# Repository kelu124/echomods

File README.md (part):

# What is this project? 

This project has a specific target of providing a __low-cost, open source technological kit to allow scientists, academics, hackers, makers or OSHW fans to hack their way to ultrasound imaging__ - below 500$ - at home, with no specific equipment required. For complementary sources of information, you can visit:

* the [github repo](https://github.com/kelu124/echomods/), for the source files, raw data and raw experiment logs;
* the [online manual/book](https://www.gitbook.com/book/kelu124/echomods/details) for a easily readable and searchable archive of the whole work;
  * with [list of probes](/include/probes/)
  * and [list of experiments](/include/experiments/)
* the [hackaday page](https://hackaday.io/project/9281-murgen-open-source-ultrasound-imaging), where I tried to blog day-to-day experiments in a casual format;
* an [article summarizing the experiment on the Journal of Open Hardware](http://openhardware.metajnl.com/articles/10.5334/joh.2/) - [DOI:10.5334/joh.2]( http://doi.org/10.5334/joh.2);
* the [slack channel if you want to discuss](https://join.slack.com/t/usdevkit/shared_invite/zt-2g501obl-z53YHyGOOMZjeCXuXzjZow);
* the Tindie store for the [analog processing unit](https://www.tindie.com/products/kelu124/ultrasound-imaging-analog-processing-module/) and the [unipolar pulser](https://www.tindie.com/products/kelu124/ultrasound-unipolar-high-voltage-pulser/) or [the motherboard](https://www.tindie.com/products/kelu124/ultrasound-modules-motherboard/).
* And of course, the [ice40 research board](https://www.tindie.com/products/kelu124/un0rick-open-ice40-ultrasound-imaging-dev-board/), on [un0rick.cc](http://un0rick.cc) and its [doc](http://doc.un0rick.cc) or even [its github](https://github.com/kelu124/un0rick). _It's a bit cheaper, and has better specs_. 

* __Disclaimer #0__: __This is not a medical ultrasound scanner__! It's a development kit that can be used for pedagogical and academic purposes - possible immediate use as a non-destructive testing (NDT) tool, for example in metallurgical crack analysis. As in all electronics, be [careful](/WordOfCaution.md).
* __Disclaimer #1__: though an engineer, this project is the first of its sort, I never did something related. It's all but a finalized product.
* __Disclaimer #2__: Ultrasound raises questions. In case you build a scanner, use caution and good sense!
* __Disclaimer #3__: This project is not part of echopen.

# Principles of ultrasound imaging

## General principles of ultrasound imaging

### Using echoes to map interfaces

Medical ultrasound is based on the use of high frequency sound to aid in the diagnosis and treatment of patients. Ultrasound frequencies range from 2 MHz to approximately 15 MHz, although even higher frequencies may be used in some situations.

The ultrasound beam originates from mechanical oscillations of numerous crystals in a transducer, which are excited by electrical pulses (piezoelectric effect). The transducer converts one type of energy into another (electrical <--> mechanical/sound). 

The ultrasound waves (pulses of sound) are sent from the transducer, propagate through different tissues, and then return to the transducer as reflected echoes when crossing an interface. The returned echoes are converted back into electrical impulses by the transducer crystals and are further processed - _mostly to extract the enveloppe of the signal, a process that transforms the electrical signal in an image_ -  in order to form the ultrasound image presented on the screen.

Ultrasound waves are reflected at the surfaces between the tissues of different density, the reflection being proportional to the difference in impedance. If the difference in density is increased, the proportion of reflected sound is increased and the proportion of transmitted sound is proportionately decreased.

If the difference in tissue density is very different, then sound is completely reflected, resulting in total acoustic shadowing. Acoustic shadowing is present behind bones, calculi (stones in kidneys, gallbladder, etc.) and air (intestinal gas). Echoes are not produced on the other hand if there is no difference in a tissue or between tissues. Homogenous fluids like blood, bile, urine, contents of simple cysts, ascites and pleural effusion are seen as echo-free structures.

### Creating a 2D image

If the process is repeated with the probe sweeping the area to image, one can build a 2D image. In practice, in the setups we'll be discussing, this sweep is done with a transducer coupled to a servo, or using a probe that has an built-in motor to create the sweep.

# Necessary architecture

### Transducer

A critical component of this system is the ultrasound transducer. A typical ultrasound imaging system uses a wide variety of transducers optimized for specific diagnostic applications, but in our case, we'll limit the costs.
 
### High-Voltage Transmitters ([see the module](/retired/tobo/))

A digital transmit beamformer typically generates the necessary digital transmit signals with the proper timing and phase to produce a focused transmit signal. High-voltage pulsers quickly switch the transducer element to the appropriate programmable high-voltage supplies to generate the transmit waveform. To generate a simple bipolar transmit waveform, a transmit pulser alternately connects the element to a positive and negative transmit supply voltage controlled by the digital beamformer. More complex realizations allow connections to multiple supplies and ground in order to generate more complex multilevel waveforms with better characteristics.

### TGC + LNA = Variable-Gain Amplifier (VGA) ([see the module](/goblin/))

The LNA in the receiver must have excellent noise performance and sufficient gain. In a properly designed receiver the LNA will generally determine the noise performance of the full receiver. 

The VGA, sometimes called a time gain control (TGC) amplifier, provides the receiver with sufficient dynamic range over the full receive cycle. Ultrasound signals propagate in the body at approximately 1540 meters per second and attenuate at a rate of about 1.4dB/cm-MHz roundtrip. Immediately after an acoustic transmit pulse, the received "echo" signal at the LNA's input can be as large as 0.5VP-P. This signal quickly decays to the thermal noise floor of the transducer element. The dynamic range required to receive this signal is approximately 100dB to 110dB, and is well beyond the range of a realistic ADC. As a result, a VGA is used to map this signal into the ADC. A VGA with approximately 30dB to 40dB of gain is necessary to map the received signal into a typical 12-bit ADC used in this application. The gain is ramped as a function of time (i.e., "time gain control") to accomplish this dynamic range mapping.

### Anti-Alias Filter (AAF) and ADC ([see the module](/retired/toadkiller/))

The AAF in the receive chain keeps high-frequency noise and extraneous signals that are beyond the normal maximum imaging frequencies from being aliased back to baseband by the ADC. Many times an adjustable AAF is provided in the design. To avoid aliasing and to preserve the time-domain response of the signal, the filter itself needs to attenuate signals beyond the first Nyquist zone. For this reason Butterworth or higher-order Bessel filters are used.

The ADC used in this application is typically a 12-bit device running from 40Msps to 60Msps. This converter provides the necessary instantaneous dynamic range at acceptable cost and power levels. In a properly designed receiver, this ADC should limit the instantaneous SNR of the receiver. As previously mentioned, however, limitations in the poor-performing VGAs many times limit receiver SNR performance

## Ultrasound hardware structure

To produce an image, the modules have to create a [high voltage pulse](/retired/tobo/), which excites a [transducer](/retroATL3/). Echoes coming from the body are amplified using a [TGC + LNA](/goblin/), which cleans the analog signal, which itself [gets digitalized](/retired/toadkiller/). 

The diagram is represented below:

# Un0rick, the ice40 board

## Why a FPGA board ?

Non destructive testing and imaging ultrasound modalities have been around since the '50s in . More and more ultrasound-based initiative are emerging, mostly focusing on image processing - while hardware has been left behind. Several teams have produced succesful designs for the different possible uses, mostly efforts from research laboratories. Most have been used on commercial US scanners, traditionaly used as experiment platforms, but they are not cheap, and yield very little in terms of data access and control. Others have been developped in labs, but, sadly, very few have been open-sourced. Let's tackle this!

It has also been shown that simple (be it low-power, low-cost and small) can be achieved - and this, even for relatively complex systems, based on 16 to 64  parallel   channels   front-end  processing and software back-end processing (embedded PC or DSP). This makes it a bit more complex for the layman, hobbyist, or non-specialist researcher to use, not to mention the very little information that is accessible.

## Hardware specifications and features

1. __FPGA__: Lattice iCE40HX4K - TQFP 144 Package
2. __Memory__:
  * 8 Mbit SRAM, 10ns, 512 k x 16, equivalent:
      * 65 full lines of 120us at 64Msps
      * 840 lines of 120us at 10Msps, 8 bits
  * 8 Mb SPI Flash for FPGA configuration 
3. __Ultrasound processing__:
  * __VGA__: AD8331 controled by DAC
  * __Pulser__: MD1210 + TC6320
  * __ADC__: 65Msps ADC10065
    * 10 bits of data / sample
    * 2 bits of line counters
    * 4 bits of IOs (counters, ...) 
4. __Parameters__: Settings programable via USB or Raspberry Pi 
  * Type of acquisition (one line / set of lines)
  * Number of lines
  * Length of lines acquisitions
  * Delay between acquisitions
  * Pulse width 
  * Delay between pulse and beginning of acquisitions
  * 200us time-gain-compensation programmable (8 bits, from 0 to Max), every 5us
5. __Extensibility__:
  * 2 x Pmod connectors
  * SMA plug for transducers
  * RPi GPIO
6. __User Interfaces__:
  * 2 x PMOD for IOs
  * 3 x push button (with software noise debouncing)
  * Jumpers for high voltage selection
7. __Input Voltage__: 
  * 5 V from RPi or USB
  * Uses 350mA-450mA at 5V
8. __Fully Open Source__:
  * Hardware: _github repository_
  * Software: _github repository_
  * Toolchain: _Project IceStorm_
  * Documentation: _gitbook_
9. __Operating Voltage__: 
  * FPGA and logics at at 3.3 V
  * High voltage at 25V, 50V, 75V
10. __Dimensions__: @todo!
11. __Weight__: @todo! 

## Comparative

| Tool           	| Murgen 	| echOmods        	| unoric               	|
|----------------	|--------	|-----------------	|----------------------	|
| Open Source    	| Yes    	| Yes             	| Yes                  	|
| ADC            	| 20Msps 	| 1Msps to 24Msps 	| 65Msps up to 100Msps 	|
| Onboard memory 	| 300 Mb 	| 10 Mb           	| 20Mb                 	|
| Price of a set	| 400$		| 450$			| 400$			|
| Modular		| Np		| Yes			| No			| 

# Modules

## What are the arduino-like ultrasound module ?

__Creating modules to facilitate ultrasound hacking__ : the principles of the echOmods is to enable a full chain of ultrasound image processing and hardware control.

We have chosen to use a module approach to make sure that each key component inside ultrasound image processing can easily be replaced and compared with another module, while providing logical _logic blocks_ and corresponding interfaces for these modules to communicate. There's a module for [high-voltage pulsing](/retired/tobo/), one for the [transducer](/retroATL3/), one for the [analog processing](/goblin/), one for [data acquisiton](/retired/toadkiller/), ... and many more!

## What images does it give ?

## What does it look like?

The modules sit on a breadboard, and communicate through the tracks laying below. The configuration represented below show the Basic dev kit.

and used in a wider context:

# A recap of the modules 

| ThumbnailImage | Name | In | Out |
|------|-------|----|------|
||**[retroATL3](/retroATL3/Readme.md)**: The aim of this echOmod is to get the mechanical movement of the piezos. Salvaged from a former ATL3.|<ul><li>ITF-A_gnd</li><li>ITF-F_12V</li><li>ITF-N_cc_motor_pwm</li><li>ITF-mET_Transducer</li><li>Motor</li><li>Tri-Piezo Head</li></ul>|<ul><li>Motor</li><li>ITF-mET_Transducer</li><li>Tri-Piezo Head</li></ul>|
||**[elmo](/elmo/Readme.md)**: The aim of this module is to achieve 20Msps, at 9bits or more. |<ul><li>ITF-1_GND</li><li>ITF-2_VDD_5V</li><li>ITF-19_3.3V</li><li>ITF-12_RPIn</li></ul>|<ul><li>Signal Digitalized</li></ul>|
||**[goblin](/goblin/Readme.md)**: The aim of this echOmod is to get the signal coming back from a transducer, and to deliver the signal, analogically processed, with all steps accessible to hackers. |<ul><li>ITF-1_GND</li><li>ITF-2_VDD_5V</li><li>ITF-7_GAIN</li><li>ITF-4_RawSig</li><li>ITF-3_ENV</li><li>ITF-18_Raw</li><li>ITF-mET_SMA</li></ul>|<ul><li>ITF-4_RawSig</li><li>ITF-3_ENV_signal_envelope</li><li>ITF-mEG_SPI</li></ul>|
||**[lite.tbo](/lite.tbo/Readme.md)**: The aim of this echOmod is to get the HV Pulse done.|<ul><li>ITF-1_GND</li><li>ITF-2_VDD_5V</li><li>ITF-9_Pon</li><li>ITF-10_Poff</li><li>ITF-19_3.3V</li><li>ITF-mET_Transducer</li></ul>|<ul><li>ITF-18_Raw</li><li>ITF-mET_SMA</li><li>ITF-mET_Transducer</li></ul>|
||**[lit3rick](/lit3rick/Readme.md)**: The aim is to summarize all modules in a all-inclusive board. Fast ADC, good load of memory, good SNR.. the not-so-DIY module, as it comes already assembled with nothing to do. Based on up5k.|||
||**[matty](/matty/Readme.md)**: The aim is to summarize all modules in a all-inclusive board. Fast ADC, good load of memory, good SNR.. the not-so-DIY module, as it comes already assembled with nothing to do =)|||
||**[doj](/doj/Readme.md)**: Getting a motherboard: that's fitting all the modules in an easy way, with an easy access to all tracks. See this for the Kicad files.|||
||**[wirephantom](/wirephantom/Readme.md)**: Just a phantom for calibrated signals|<ul><li>na</li></ul>|<ul><li>na</li></ul>|
||**[silent](/silent/Readme.md)**: The aim of this echOmod is to simulate a raw signal that would come from the piezo and analog chain.|<ul><li>ITF-1_GND</li><li>ITF-2_VDD_5V</li><li>ITF-17_POff3</li></ul>|<ul><li>ITF-18_Raw</li></ul>|

# List of experiments

# Experiments

 * 2021-04-25: [Annular MUXed](/include/experiments/auto/20210425a.md): testing an annular transducer on a pink phantom _(20210425a)_
 * 2021-04-24: [BiVi piezo on the MUX](/include/experiments/auto/20210424a.md): First tests of the MUX _(20210424a)_
 * 2021-01-29: [`Tri` two probes](/include/experiments/auto/20210129a.md): Tri's tests with two probes _(20210129a)_
 * 2020-12-23: [test probes](/include/experiments/auto/20201223a.md): testing probes with un0usb _(20201223a)_
 * 2020-12-19: [test piezos](/include/experiments/auto/20201219r.md): VNAs piezos (dismanted ones) _(20201219r)_
 * 2020-11-28: [hp2121 matching](/include/experiments/auto/20201128a.md): checking hp2121 probe impedance matching _(20201128a)_
 * 2020-11-08: [impedance matching](/include/experiments/auto/20201108a.md): testing two piezos with impedance matching network _(20201108a)_
 * 2020-11-07: [lib 025](/include/experiments/auto/20201107a.md): NDT presentation - un0rick & usb _(20201107a)_
 * 2020-11-04: [lib 024](/include/experiments/auto/20201104a.md): Basics on - un0rick & usb _(20201104a)_
 * 2020-11-03: [Impedance matching](/include/experiments/auto/20201103a.md): Interesting results for impedance matching. _(20201103a)_
 * 2020-10-31: [Pulse width calculation](/include/experiments/auto/20201031a.md): how to get the best echo as a function of pulser waveform _(20201031a)_
 * 2020-10-28: [strange issues pyUn0](/include/experiments/auto/20201028a.md): seems CS does not work _(20201028a)_
 * 2020-10-26: [usb firmware](/include/experiments/auto/20201026a.md): testing it works with un0rick _(20201026a)_
 * 2020-10-24: [i2s issue](/include/experiments/auto/20201024a.md): Exploring the i2s offsets _(20201024a)_
 * 2020-10-23: [Canada](/include/experiments/auto/20201023a.md): `Silvio` first lit3rick tests _(20201023a)_
 * 2020-10-22: [Spain](/include/experiments/auto/20201022a.md): `Jorge` tests on lit3rick _(20201022a)_
 * 2020-10-08: [benchmark lit3 and un0](/include/experiments/auto/20201008a.md): Running acquisitions on the same rig. _(20201008a)_
 * 2020-08-09: [bard vna](/include/experiments/auto/20200809r.md): bard vna tests _(20200809r)_
 * 2020-08-08: [all probes vna](/include/experiments/auto/20200808r.md): getting impedance params of all probes _(20200808r)_
 * 2020-06-08: [brd35 test](/include/experiments/auto/20200608a.md): testing an electromagnetic movement probe _(20200608a)_
 * 2020-05-08: [testing bard probe](/include/experiments/auto/20200508a.md): Nothing much really _(20200508a)_
 * 2020-04-21: [a-law](/include/experiments/auto/20200421b.md): testing a-law compressions compared to log and sqrt _(20200421b)_
 * 2020-04-21: [comparing boards](/include/experiments/auto/20200421a.md): preliminary check between lit3rick and un0rick _(20200421a)_
 * 2020-04-18: [echo-tomo](/include/experiments/auto/20200418a.md): Trying to get a tomo echo image _(20200418a)_
 * 2020-04-16: [testing new piezos](/include/experiments/auto/20200416a.md): and calibrating new piezos against bubbles _(20200416a)_
 * 2020-03-25: [NDT pulse widths](/include/experiments/auto/20200325a.md): Trying and getting different pulse on a steel block. _(20200325a)_
 * 2020-03-21: [pulse widths](/include/experiments/auto/20200321a.md): Trying and getting different pulse on the test bench. _(20200321a)_
 * 2019-10-27: [lit3rick De.bin](/include/experiments/auto/20191027b.md): New success with lit3rick, with dynamic DAC _(20191027b)_
 * 2019-10-27: [meh - noisy](/include/experiments/auto/20191027a.md): still some tests, Dd.bin for lit3rick _(20191027a)_
 * 2019-10-26: [meh C2w](/include/experiments/auto/20191026a.md): testing new bins for lit3rick _(20191026a)_
 * 2019-10-24: [getting better at dyn dac](/include/experiments/auto/20191024a.md): tests _(20191024a)_
 * 2019-10-23: [lit3 success](/include/experiments/auto/20191023a.md): Some better acquisitions - it works ! _(20191023a)_
 * 2019-10-22: [lit3 weird](/include/experiments/auto/20191022b.md): Strange signals ahead _(20191022b)_
 * 2019-10-22: [weird acqs again](/include/experiments/auto/20191022a.md): investigating _(20191022a)_
 * 2019-10-18: [first un0 acqs from Tri](/include/experiments/auto/20191018a.md): his [setup seems to work](https _(20191018a)_
 * 2019-10-16: [weird acqs](/include/experiments/auto/20191016a.md): what is wrong with me ? _(20191016a)_
 * 2019-10-06: [lit3 questions](/include/experiments/auto/20191006a.md): what is happening ? _(20191006a)_
 * 2019-08-04: [tuto video for Un0rick](/include/experiments/auto/20190804a.md): [more here on youtube](https _(20190804a)_
 * 2019-07-13: [new un0 batch](/include/experiments/auto/20190713b.md): quality tests _(20190713b)_
 * 2019-07-13: [RPI3](/include/experiments/auto/20190713a.md): yes, I had to test _(20190713a)_
 * 2019-04-15: [NDT tests](/include/experiments/auto/20190415a.md): testing what the NDT probes does _(20190415a)_
 * 2019-04-04: [NDT tests double peak](/include/experiments/auto/20190404a.md): why are there two frequencies ? _(20190404a)_
 * 2019-03-29: [NDT dual transducer](/include/experiments/auto/20190329a.md): understanding the transducer _(20190329a)_
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
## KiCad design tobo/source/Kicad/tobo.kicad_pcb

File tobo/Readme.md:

---
module: tobo
author: kelu124
---

# Module: Tobo

## Name

[`MDL-tobo_hvpulser`]()

## Title

Tobo: the HV-pulser

## Description

* The HV-Pulser of the echOmods
* Setup? Have a look at the [quick start guide](/tobo/QuickStart.md)
* version: V0.2
* cost:120$
* sourcing:Custom made, get the [Gerbers](/tobo/source/), [buy it preassembled on tindie](https://www.tindie.com/products/kelu124/ultrasound-imaging-pulser-module/) or contact @kelu124
* date: 24/04/2016
* technology: Module-compatible, Homemade PCB, ICs based on `HV7360` and `R05-100B`
* language: Altium
* author: Kelu124

## IOs

### Inputs

* `ITF-1_GND`
* `ITF-2_VDD_5V`
* `ITF-9_Pon` 
* `ITF-10_Poff` 
* `ITF-19_3.3V`
* `ITF-mET_Transducer` : signal coming back	

### Outputs

* `ITF-18_Raw`  : for the signal coming from the transducer
* `ITF-mET_SMA` : for the signal coming out to the signal processing (if through SMA)
* `ITF-mET_Transducer` : for the signal coming out of the pulser (if through SMA)

## Key Components

* `HV7360`
* `R05-100B`

## Information

### What is it supposed to do?

The aim of this echOmod is to get the HV Pulse done.

### How does it work: block diagram

* `ITF-9_Pon`->`HV7360`
* `ITF-10_Poff`->`HV7360`
* `ITF-2_VDD_5V`->`R05-100B`->`HV7360`->`ITF-mET_Transducer`
* `ITF-mET_Transducer`->`ITF-mET_SMA`
* `ITF-mET_Transducer`->`ITF-18_Raw`

## About the module

### Pros

* Only needs 5V and 3.3V
* Energy use : TODO
* Using any logic voltage for PulseOn and PulseOff is a pplus
* Can use the potentiometer to control the tension
* Modularity through jumpers and SMA

### Cons

* Takes a lot of space because of the modularity. SMA, jumpers and pots could be removed.

* Little flexibility from the use of ICs.
* There's no impedance matching for the pulser to the transducer, could be better.

## Constraint and limits

### The pulser-control

### Output signal

### With and without a pulser - no impedance adaptation

### Look of the schematics

and [a link to it](/tobo/tobo_schematics.pdf) (plus some bonus with the [map](/tobo/tobo_map.PDF)). 

Source files include [Altium](/tobo/source/Tobo-Altium-II.zip) and [KiCad](/tobo/source/Tobo-Kicad.zip) - along with the [BOM](/tobo/source/tobo_bom.xls).

### Look of the actual board

### Availability of HV7360

* Some issues with the availability of the `HV7360`, living its end of life. The latest version of [Altium](/tobo/source/Altium/) and [Kicad](/tobo/source/Kicad/) source files should show the new [HV7360 CABGA](/tobo/datasheets/HV7360_CABGA.pdf).
* However, this latest should be available officially in Jan 2017.

### Setting up the module

Setup? Have a look at the [quick start guide](/tobo/QuickStart.md) on how to prepare the pulser.

### On the way towards a simpler board

[The alt design](/alt.tbo/) (and the corresponding [the schematics](/alt.tbo/draft.alt.tobo.v0.01.pdf)  + [BOM](/alt.tbo/source/v2/BOM.v2.macrofab.xlsx) ).

## Discussions

### TODO

### DONE

* Writing specs 
* HV7360 has been updated
* Sending microcircuits to Edgeflex
* Agreeing on the strips/tracks 
* Defining the ICs to use to pulse
* Getting schematics
* Publishing schematics
* Receive the module
* Test it with different transducers
* Publish the sources in KiCAD

### People

* Sofian (for preparing the field with Murgen)

## License

### echOmods 

The [echOmods project](https://github.com/kelu124/echomods) and its prototypes (amongst which we find the [Tobo](/tobo/) module) are open hardware, and working with open-hardware components.

Licensed under TAPR Open Hardware License (www.tapr.org/OHL)

Copyright Kelu124 (kelu124@gmail.com) 2015-2018

### Based on 

The following work is base on a previous TAPR project, [Murgen](https://github.com/kelu124/murgen-dev-kit) - and respects its TAPR license.

Copyright Kelu124 (kelu124@gmail.com) 2015-2018

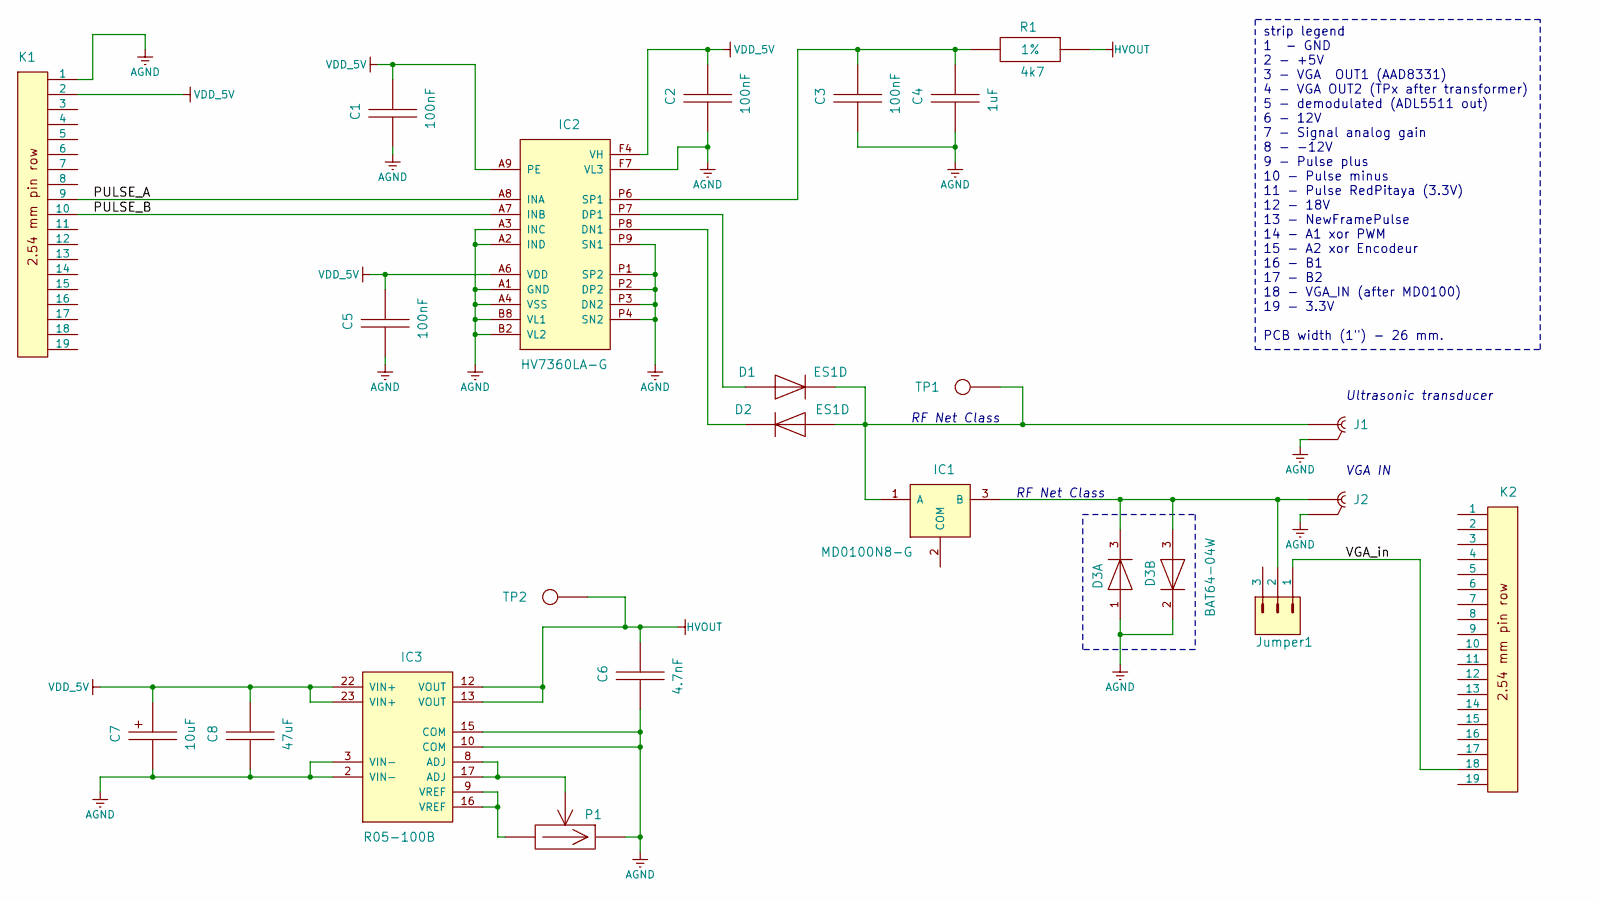
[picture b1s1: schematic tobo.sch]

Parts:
C1, C2, C3, C5: Capacitor; SM0603_3D_cap
C4: Capacitor; CAPC5650X165N; Tolerance ±10%; Voltage 200V; Manufacturer Part Number CC2220_1UF_200V_10%_X7R
C6: Capacitor; CAPC2012X110N; Tolerance ±10%; Voltage 250V; Manufacturer1 Part Numb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 GRM21AR72E472KW01D
C7: Capacitor_polar; CAPMP3528X210N; Tolerance ±10%; Voltage 16V; Manufacturer Part Number CTE3528-21_10UF_16V_10%_LESR0800
C8: Capacitor; CAPC3216X180N; Tolerance ±20%; Voltage 25V; Manufacturer Part Number C3216X5R1E476M160AC
D1, D2: Diode; DIOM5027X244N; Voltage 200V; Part Description Fast Rectifier
D3: BAT64-04W; SOT65P210X100-3N; Voltage 40V; Part Description Silicon Schottky Double Diode
IC1: MD0100N8-G; SOT89; Part Description Ultra-Sound HV Switch
IC2: HV7360LA-G; BGA22C50P9X14_500X700X105; Part Description High Speed, ±100V 2.5A Two or Three Lev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
IC3: R05-100B; PWS_RECOM_R05-100B; Part Description +5VDC to +55-135VDC 5W Power Supply
J1, J2: SMA; AMPHENOL_132357-11; Part Description SMA End Launch Jack for 1.58mm PCB, 50 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
Jumper1: Jumper; SULLINS_GRPB031VWVN; Part Description 3 Contact 0.5\" Pitch Single-In-Line Ve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
K1, K2: Header19; PLS_2.54mm-19
P1: TrimPot; TRIM_BOURNS_3223W; Tolerance ±20%; Part Description 11 Turns SMD Trimpot® Trimming Potentio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
R1: Resistor; RESC3216X65N; Tolerance_Show 1%; Tolerance ±1%; Part Description General Purpose Thick Film Chip Resistor
TP1, TP2: TP; NICOMATIC_C12000B; Part Description SMD Test Point

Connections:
/PULSE_A: IC2.A8 (INA), K1.9
/PULSE_B: IC2.A7 (INB), K1.10
/VGA_in: Jumper1.1, K2.18
AGND: C1.2, C2.2, C3.2, C4.2, C5.2, C6.2, C7.2, C8.2, D3.1 (COMAC), D3.2 (C), IC2.A1 (GND), IC2.A2 (IND), IC2.A3 (INC), IC2.A4 (VSS), IC2.B2 (VL2), IC2.B8 (VL1), IC2.F7 (VL3), IC2.P1 (SP2), IC2.P2 (DP2), IC2.P3 (DN2), IC2.P4 (SN2), IC2.P9 (SN1), IC3.2 (VIN-), IC3.3 (VIN-), IC3.10 (COM), IC3.15 (COM), J1.2, J2.2, K1.1, P1.3 (CW)
HVOUT: C6.1, IC3.12 (VOUT), IC3.13 (VOUT), R1.1, TP2.1
unnamed: C3.1, C4.1, IC2.P6 (SP1), R1.2
unnamed: D1.1 (C), D2.2 (A), IC1.1 (A), J1.1, TP1.1
unnamed: D1.2 (A), IC2.P7 (DP1)
unnamed: D2.1 (C), IC2.P8 (DN1)
unnamed: D3.3 (C), IC1.3 (B), J2.1, Jumper1.2
unnamed: IC3.9 (VREF), IC3.16 (VREF), P1.1 (CCW)
unnamed: IC3.8 (ADJ), IC3.17 (ADJ), P1.2 (W)
VDD_5V: C1.1, C2.1, C5.1, C7.1, C8.1, IC2.A6 (VDD), IC2.A9 (PE), IC2.F4 (VH), IC3.22 (VIN+), IC3.23 (VIN+), K1.2

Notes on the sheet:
strip legend 1 - GND 2 - +5V 3 - VGA OUT1 (AAD8331) 4 - VGA OUT2 (TPx after transformer) 5 - demodulated (ADL5511 out) 6 - 12V 7 - Signal analog gain 8 - -12V 9 - Pulse plus 10 - Pulse minus 11 - Pulse RedPitaya (3.3V) 12 - 18V 13 - NewFramePulse 14 - A1 xor PWM 15 - A2 xor Encodeur 16 - B1 17 - B2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
RF Net Class
VGA IN
Ultrasonic transducer

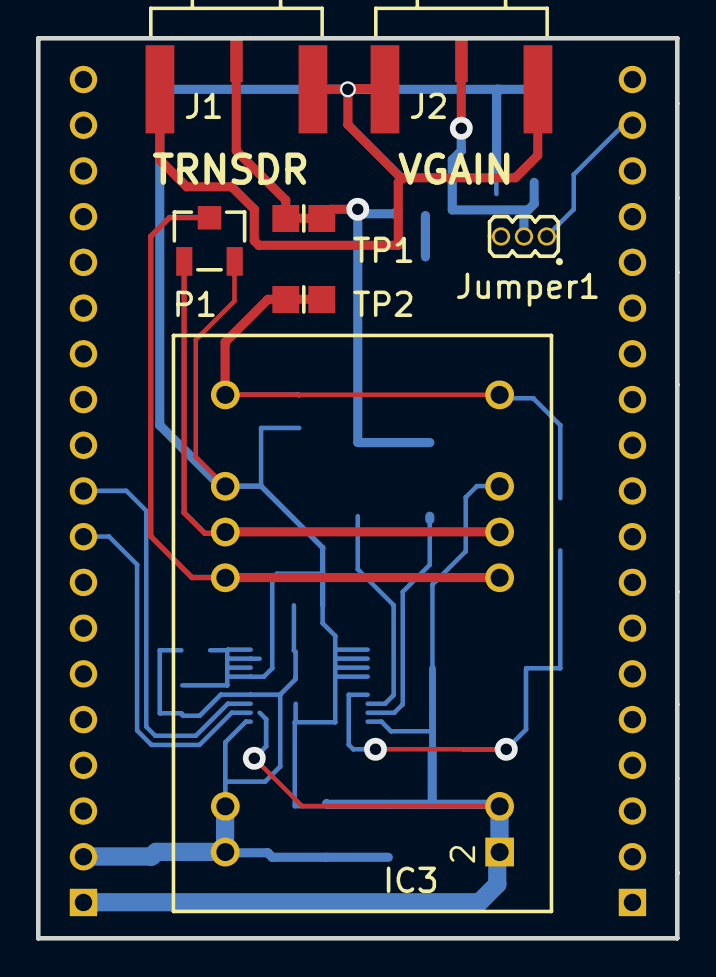
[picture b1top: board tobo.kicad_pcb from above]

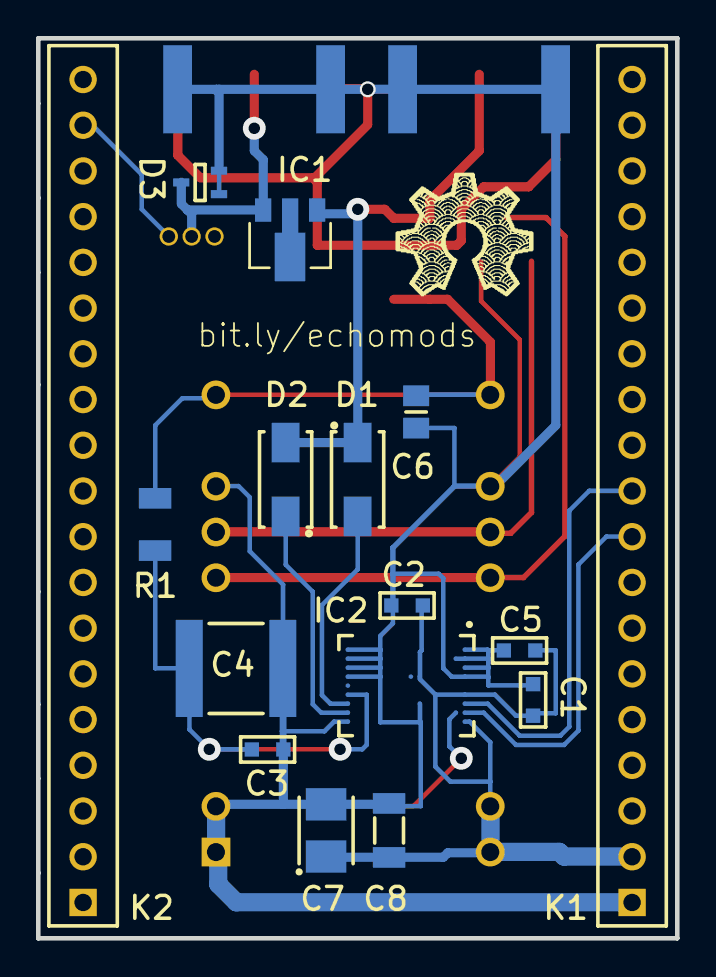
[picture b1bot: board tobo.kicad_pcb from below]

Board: 2 copper layers, 35.5 x 50.0 mm, 23 parts (16 on the bottom side), 13 nets.

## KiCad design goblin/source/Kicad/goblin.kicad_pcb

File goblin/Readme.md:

# Module: Goblin 

## Name

[`MDL-goblin_tgcenvadc`]()

## Title

Goblin: a TGC-Envelop-ADC module

## Description

* The analog signal-processing heart of the echOmods
* Setup? Have a look at the [quick start guide](/goblin/QuickStart.md)
* version: V0.2
* date: 25/12/2016
* cost:149$
* sourcing:Custom made, get the [Gerbers](/goblin/source/), or [buy it preassembled on Tindie](https://www.tindie.com/products/kelu124/ultrasound-imaging-analog-processing-module/), or contact @kelu124
* technology: Module-compatible, Homemade PCB, ICs based on `AD8331` and `ADL5511`
* language: Altium, Kicad
* author: Kelu124

## IOs

### Inputs

* `ITF-1_GND`
* `ITF-2_VDD_5V`
* `ITF-7_GAIN`
* `ITF-4_RawSig` : because it's used internally
* `ITF-3_ENV` : because it's used internally
* `ITF-18_Raw` : for the signal coming from the pulser (if through track 18)
* `ITF-mET_SMA` : for the signal coming from the pulser (if through SMA)

### Outputs

* `ITF-4_RawSig`: Amplified Raw Signal, post TGC, before the enveloppe detection	
* `ITF-3_ENV_signal_envelope`: enveloppe of the signal, post TGC
* `ITF-mEG_SPI` : signal from the ADC

## Key Components

* `ADL5511`: Enveloppe detection 
* `AD8331`: TGC
* `AD7274`: 2Msps SPI ADC
* `AD8691`: OA

## Information

### What is it supposed to do?

The aim of this echOmod is to get the signal coming back from a transducer, and to deliver the signal, analogically processed, with all steps accessible to hackers. 

With more details, this [Goblin](/goblin/) board aims at getting a signal, and giving access to key points within the signal processing chain for ultrasound imaging, namely:

* Getting access to a TGC
* Getting the enveloppe of the signal
* Cleaning the signal before feeding in the on-board SPI ADC

All key signals are accessible, and jumpers, as well as pots, enable on-board fine-tuning of the signals. [See more details on the __testing session__, to see the behavior of the board on a oscillo](/goblin/2016-07-08.md).

It's also a first try at a SPI ADC. Using a up to 3 Msps one in order to catch only the enveloppe, to be tested with other uC, RPi or BBB. Test have been also done with [6MSps, arduino IDE-compatible, STM32](/retired/croaker/). 
	
### How does it work: block diagram

* `ITF-7_GAIN`->`Goblin_Jumper2`->`AD8331`->`ITF-C_amplified_raw_signal`->`ADL5511`->`ITF-3_ENV`->`AD8691`->`ITF-Ext_Amplified`->`AD7274`->`ITF-mEG_SPI`
* `ITF-18_Raw`->`Goblin_Jumper1`->`AD8331`
* `ITF-mET_SMA`->`Goblin_Jumper1`
* `ITF-InternalPot1_gain_control`->`Goblin_Jumper2`
* `ITF-InternalPot2_ADC_Vref`->`AD7274`
* `ADL5511`->`Int-Offset`->`AD8691`

This can be summarized below - all the signals represented are accessible via separate on-board pins:

Input/Output:

## About the module

### Pros

* Only needs 5V and 3.3V inputs.
* Energy use is relatively low: at 9V, Tobo, Goblin, and a trinket pro ask for 180mA.
* _ADC V_REF_ is flexible: better resolution in output of the ADC
* _E_REF_ is being removed from the signal output, better than Murgen, where we lost 1.1V from the signal range.
* ADC is http://fr.farnell.com/jst-japan-solderless-terminals/b6b-ph-k-s-lf-sn/embase-entree-sup-6-voies/dp/9492453?MER=sy-me-pd-mi-alte -- what appropriate connector ? http://fr.farnell.com/jst-japan-solderless-terminals/vhr-6n/boitier-connecteur-rcpt-6pos-1/dp/2399220 ?

### Cons: what to to make better

* Takes a lot of space because of the modularity. Jumpers and pots could be removed, not to mention SMA.
* The amplifier removing E_REF brings in some noise: a filter could be used there to remove to high frequencies.
* The SMA brings little, but still a noise analysis could be done to assess the difference between routing the signal through a SMA cable or through the pins.
* There are only two layers. A fourth one to connect each pin to the other pin on the same row, as well as a ground plane, could help with the noise.
* Little flexibility from the use of ICs - but sufficient of sorts for our use.
* The [ADC](/goblin/datasheets/AD7274 - 7273 7276.pdf) is borderline in terms of speed of use. A higher sampling rate could be useful.
* There was a bug 	with the [ADL5511](/goblin/datasheets/ADL5511.pdf): need to know how it shuts down.

### Detailed view

#### BEWARE

The transfo has been updated (see [this folder for a version with an easily found transfo](/goblin/source/Altium.v2/) - __untested yet__).

#### Explained

#### In/Out

See more details of the [acquisition of in/out of the module, using the PRUDAQ Module](/retired/toadkiller/data/test_enveloppe/Readme.md).

#### Comparing the signals: amplified signal vs enveloppe detected

The overall signal

Details

Details on the peaks

#### Schematics

## Constraint and limits

### Tests

#### Access to raw data

Data sampled at 10Msps on the [PRUDAQ](/retired/toadkiller/) on both channels.

See the Jupyter notebook [In-Out.ipynb](/retired/toadkiller/data/test_enveloppe/In-Out.ipynb)

Data is saved [here](/retired/toadkiller/data/test_enveloppe/dual_entry.bin). It's 32Mb of sampling at 10 Msps. Full repo for the [measure test](/retired/toadkiller/data/test_enveloppe/). Let's check the Signal In vs Signal Out:

with details:

#### Trying with different frequencies

##### At 3 MHz

##### At 5MHz

##### At 7.5MHz

##### At 10MHz

#### Difference between enveloppe and ADC input?

-> the offset is removed, there's also a small gain (x2).

See below: there's an offset at the enveloppe detection (~RMS), which is removed. Enveloppe is 500mV before, comes at 1V+ afterwards.

##### Before the AOP

##### After the AOP

### Idea for onboard ADC

The AD7273/AD7274 are high speed, low power, 10-/12-bit, single supply ADCs, respectively. The parts can be operated from a 2.35 V to 3.6 V supply. When operated from any supply voltage within this range, the AD7273/AD7274 are capable of throughput rates of 3 MSPS when provided with a 48 MHz clock. 

## Discussions

### TODO

* Test Goblin v2

### DONE

* Check the power consumption
* [Testing the in and out signals](/retired/toadkiller/data/test_enveloppe/) of the board with the prudaq.
* Specs to write
* Agreeing on the strips 
* Check if 5V and 3.3V are stable
* Defining the ICs to use
* Getting schematics
* Send microcircuits to Edgeflex
* Receive the module
* Publish the sources in KiCAD (@Sofian maybe?)
* CANCELLED - Test it with the [EMW3165](/retired/hannin/)
* Plug it to a [RPi0](/elmo/) or [BBB](/retired/toadkiller/) or [STM32](/retired/croaker/)
* Connect the ADC to a RPi0

### People

* Sofian (for preparing the field with Murgen)
* Vlad for his expertise with Altium

## License

### Goblin 

The [echOmods project](https://github.com/kelu124/echomods) and its prototypes (so Goblin) are open hardware, and working with open-hardware components.

Licensed under TAPR Open Hardware License (www.tapr.org/OHL)

Copyright Kelu124 (kelu124@gmail.com) 2015-2018

### Based on 

The following work is base on a previous TAPR project, [Murgen](https://github.com/kelu124/murgen-dev-kit) - and respects its TAPR license.

Copyright Kelu124 (kelu124@gmail.com) 2015-2018

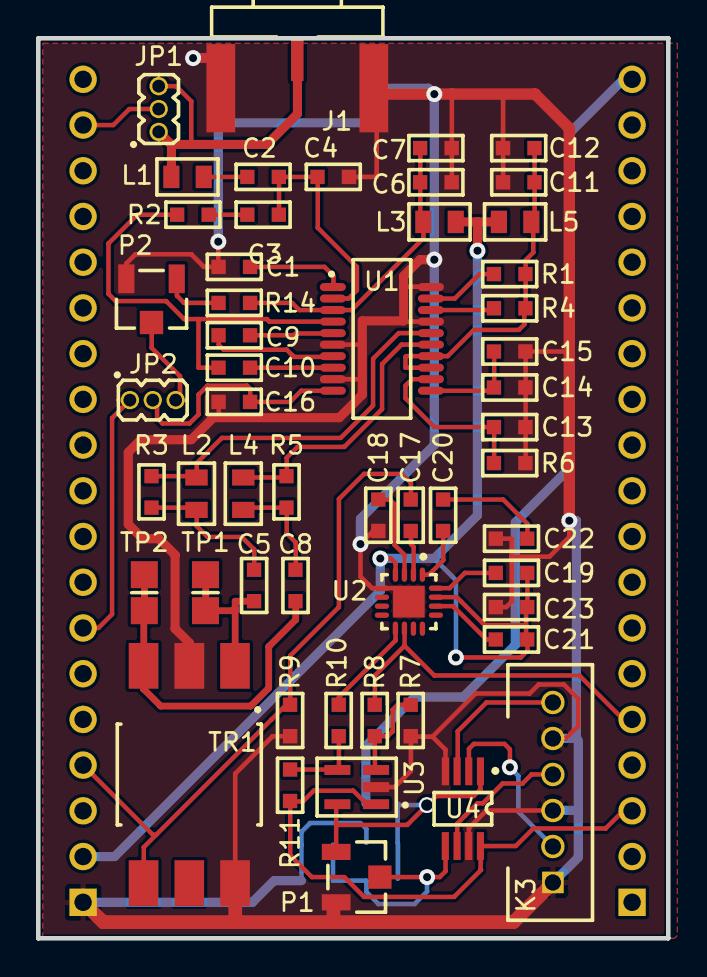
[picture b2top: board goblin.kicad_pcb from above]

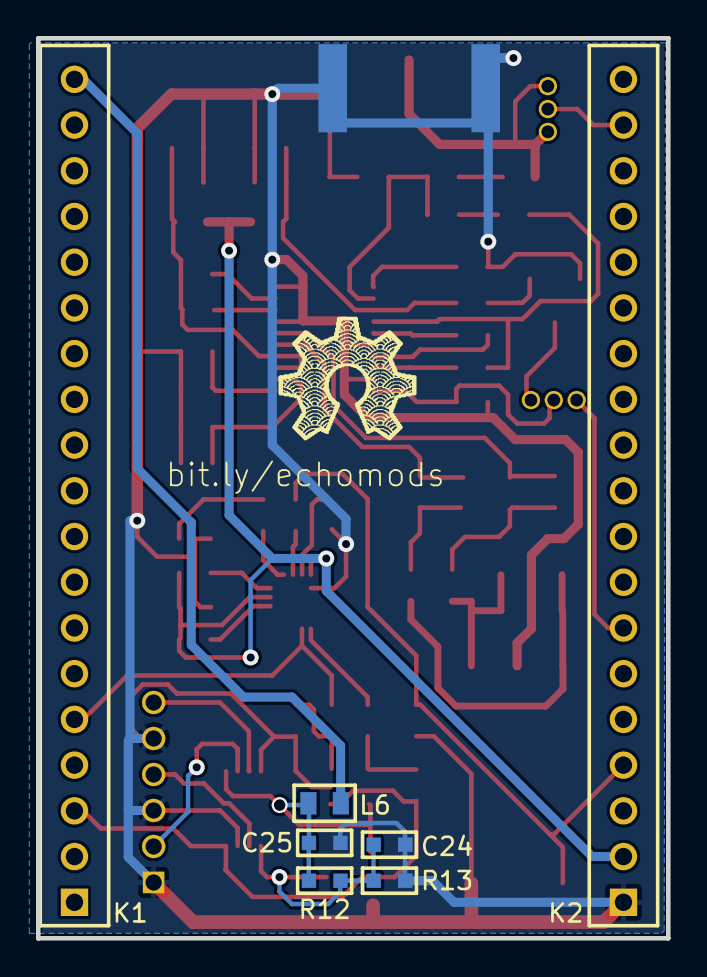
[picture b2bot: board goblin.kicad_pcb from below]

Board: 2 copper layers, 35.0 x 50.0 mm, 60 parts (7 on the bottom side), 46 nets.

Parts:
C1, C2, C3, C4, C5, C6, C7, C8, C9, C10, C11, C12, C13, C14, C15, C16, C17, C18, C19, C20, C21, C22, C23, C24, C25: Capacitor; SM0603_3D_cap
J1: SMA; AMPHENOL_132357-11
Jumper1, Jumper2: Jumper; SULLINS_GRPB031VWVN
K1, K2: Header19; PLS_2.54mm-19
K3: Header6; Molex_89400-061
L1, L2, L3, L4, L5, L6: Inductor; SM_0805_INDUCTANCE_3D
P1, P2: TrimPot; TRIM_BOURNS_3223W
R1, R2, R3, R4, R5, R6, R7, R8, R9, R10, R11, R12, R13, R14: Resistor; SM0603_3D_res
TP1, TP2: TP; NICOMATIC_C12000B
TR1: RF_Transformer_1; XFMR_MINI-CIRCUITS_KK81
U1: AD8331ARQZ; SOP64P600X175-20N
U2: ADL5511ACPZ-R7; QFN50P300X300X80-17N-S175
U3: AD8691; TSOT-5(RT-5)
U4: AD7274; RM-8

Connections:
3.3VA: C25.1, L6.2, P1.1, R12.1, U3.5, U4.1
/ADC: K1.3, R11.1, U3.1, U4.8
/ADC_VREF: C24.1, P1.2, R12.2, R13.1, U4.5
/GAIN: Jumper2.1, K2.7
/VGA_IN: Jumper1.2, K2.18
/VGA_OUT2: C17.2, K2.4, R9.1, TR1.4
/VGA_OUT_N: C5.2, TP1.1, TR1.1
/VGA_OUT_P: C8.2, TP2.1, TR1.3
/V_ENVELOPE: K1.5, R8.2, U2.10
AGND: C1.2, C4.2, C6.2, C7.2, C11.2, C12.2, C13.2, C14.2, C15.2, C16.2, C18.2, C22.2, C23.2, C24.2, C25.2, J1.2, K2.1, K3.1, K3.3, K3.5, P1.3, P2.3, R6.2, R7.1, R9.2, R13.2, TR1.2, TR1.6, U1.6, U1.9, U1.17, U1.20, U2.5, U2.17, U3.2, U4.4, U4.7
unnamed: C1.1, U1.1
unnamed: C2.1, L1.2
unnamed: C2.2, C3.1, C4.1, U1.2
unnamed: C3.2, R2.1
unnamed: C5.1, L2.1, R3.2
unnamed: C6.1, C7.1, L3.2, R14.1, U1.3
unnamed: C8.1, L4.1, R5.2
unnamed: C9.1, U1.5
unnamed: C9.2, U1.7
unnamed: C10.1, R2.2, U1.4
unnamed: C10.2, U1.8
unnamed: C11.1, C12.1, L5.2, R1.2, R4.2, U1.13, U1.14
unnamed: C13.1, R6.1, U1.12
unnamed: C14.1, C15.1, U1.11
unnamed: C16.1, Jumper2.2, U1.10
unnamed: C17.1, U2.2
unnamed: C18.1, U2.3
unnamed: C19.1, U2.16
unnamed: C20.1, U2.1
unnamed: C20.2, C22.1
unnamed: C21.1, U2.14
unnamed: J1.1, Jumper1.1, Jumper1.3, L1.1
unnamed: Jumper2.3, P2.2
unnamed: K3.2, U4.2
unnamed: K3.4, U4.6
unnamed: K3.6, U4.3
unnamed: L2.2, R3.1, U1.16
unnamed: L4.2, R5.1, U1.15
unnamed: P2.1, R14.2
unnamed: R1.1, U1.19
unnamed: R4.1, U1.18
unnamed: R7.2, R8.1, U3.3
unnamed: R10.1, R11.2, U3.4
unnamed: R10.2, U2.9
VDD_3.3V: K1.19, L6.1
VDD_5V: C19.2, C21.2, C23.1, K2.2, L3.1, L5.1, U2.4, U2.15

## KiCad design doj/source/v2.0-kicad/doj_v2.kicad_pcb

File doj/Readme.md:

# Module: Doj 

## Name

[`MDL-echomods_motherboard`]()

## Title

The motherboard of the echomods

## Description

* The motherboard for the modules
* Setup? Have a look at the [quick start guide](/doj/QuickStart.md)
* Latest version: V2.0
* date: 04/06/2017
* technology: pcb
* language: kicad
* cost:5$
* sourcing:Anywhere for [stripboard](https://www.amazon.com/s/ref=nb_sb_noss_2?url=node%3D667846011&field-keywords=stripboard&rh=n%3A667846011%2Ck%3Astripboard). Or PCB from [OSHPark](https://oshpark.com/shared_projects/2taE6p4M) if you can order by 3. Or [straight from Tindie](https://www.tindie.com/products/kelu124/ultrasound-modules-motherboard/).
* author: Kelu124

## IOs

### Inputs

* Power supply

### Outputs

* Signal =)

## Key Components

* PCB

## Information

### What is it supposed to do?

Getting a motherboard: that's fitting all the modules in an easy way, with an easy access to all tracks. See [this](/doj/source/v2.0-kicad/) for the Kicad files.

### How does it work: block diagram

## About the module

### Pros

* Half of a A4 sheet .. that's the target!  

### Cons

* Maybe can introduce noise.

## Constraint and limits

A time-reversed storyline for the motherboard =)
 
### v2.0: A clean PCB for rasbperry

#### V2 

#### Populated

### v1.2: PCB 

With the [OSHPark](https://oshpark.com/shared_projects/2taE6p4M) PCB, coming from the [brief](/doj/old/brief.md).

### v1.1: Adding new modules

#### Loaded

#### Unloaded

### v1.0: Initial design

As in mind 

Now with the actual modules

## Discussions

### TODO

### DONE

* [PCB on OSHPark](https://oshpark.com/shared_projects/2taE6p4M)
* Having the list of strips accessible
* Design
* Change the viewme
* Assemble it
* Test it
* Adapt power supply from v2 - smaller board footprint
* Add a level shifter been Pon 3.3 and 5 and Poff 3.3 and 5
* A bit more space around the Pi0/PiW headers
* Proper silkscreening around the Pi0 headers (they are reversed)
* Jumper for the ADC in.. and selector (enveloppe and amplified signal) (either to Feather or to ADC .. and dedicated pin on Rpi)
* SPI from RPi to Oled... or SPI to screen (to be checked in both case) .. or both kept, there are two SPI

### People

* Kelu124

## License

### Doj 

The [echOmods project](https://github.com/kelu124/echomods) and its prototypes (amongst which we find the [doj](/doj/) module) are open hardware, and working with open-hardware components.

Licensed under TAPR Open Hardware License (www.tapr.org/OHL)

Copyright Kelu124 (kelu124@gmail.com) 2015-2018

### Based on 

The following work is base on a previous TAPR project, [Murgen](https://github.com/kelu124/murgen-dev-kit) - and respects its TAPR license.

Copyright Kelu124 (kelu124@gmail.com) 2015-2018

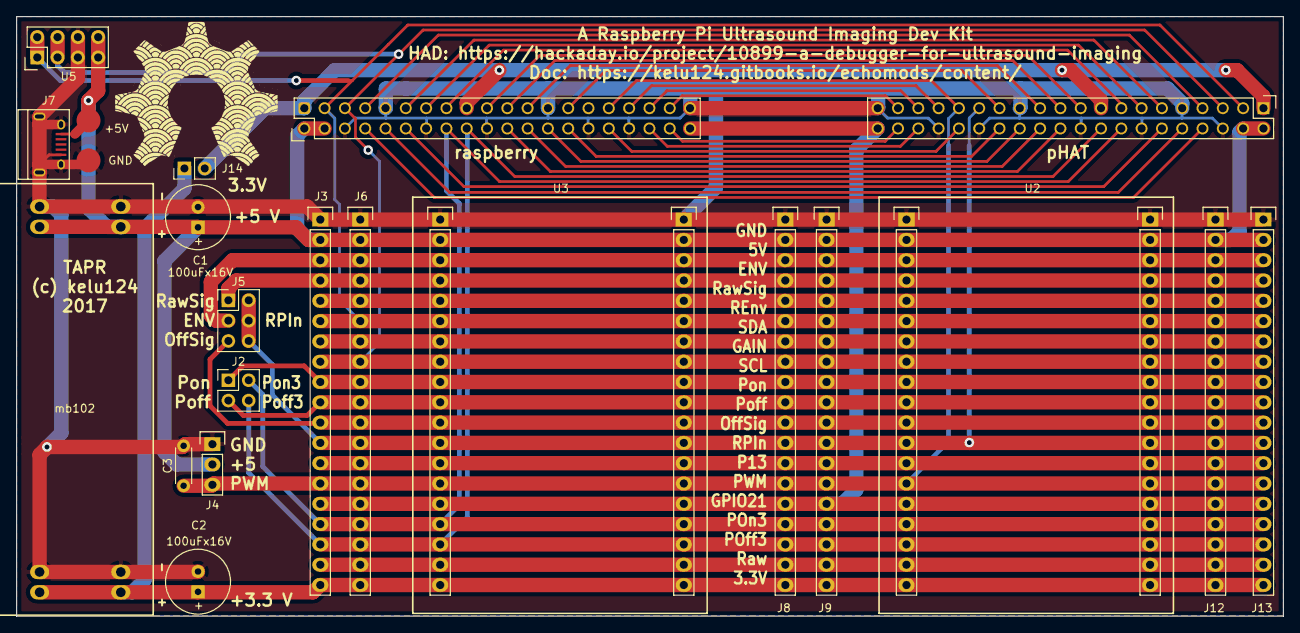
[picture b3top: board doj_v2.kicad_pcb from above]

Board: 2 copper layers, 158.5 x 75.0 mm, 24 parts (0 on the bottom side), 41 nets.

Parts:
+5V: Measurement_Point_Square-SMD-Pad_Big
C1, C2: 100uFx16V; C1V8
C3: C_Disc_D4.3mm_W1.9mm_P5.00mm
GND: Measurement_Point_Square-SMD-Pad_Big
J2: Pin_Header_Straight_2x02_Pitch2.54mm
J3, J6, J8, J9, J12, J13: Pin_Header_Straight_1x19
J4: Pin_Header_Straight_1x03
J5: Pin_Header_Straight_2x03_Pitch2.54mm
J7: USB_Micro-B
J14: Pin_Header_Straight_1x02_Pitch2.54mm
MB102: mb102
U2, U2_R, U3, U3_R: Pin_Header_Straight_1x19
U5: Pin_Header_Straight_2x04
pHAT: Pin_Header_Straight_2x20
raspberry: Pin_Header_Straight_2x20

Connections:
AGND: C1.2, C2.2, C3.2, GND.1, J3.1, J4.1, J6.1, J7.5, J7.6, J8.1, J9.1, J12.1, J13.1, MB102.1, MB102.3, MB102.5, MB102.7, U2.1, U2_R.1, U3.1, U3_R.1, U5.5, U5.6, pHAT.6, pHAT.9, pHAT.14, pHAT.20, pHAT.25, pHAT.30, pHAT.34, pHAT.39, raspberry.6, raspberry.9, raspberry.14, raspberry.20, raspberry.25, raspberry.30, raspberry.34, raspberry.39
ENV: J3.3, J5.3, J6.3, J8.3, J9.3, J12.3, J13.3, U2.3, U2_R.3, U3.3, U3_R.3
GAIN: J3.7, J6.7, J8.7, J9.7, J12.7, J13.7, U2.7, U2_R.7, U3.7, U3_R.7
GPIO21: J3.15, J6.15, J8.15, J9.15, J12.15, J13.15, U2.15, U2_R.15, U3.15, U3_R.15, pHAT.40, raspberry.40
LCD_SCL: J3.8, J6.8, J8.8, J9.8, J12.8, J13.8, U2.8, U2_R.8, U3.8, U3_R.8, U5.3, U5.4, pHAT.5, raspberry.5
LCD_SDA: J3.6, J6.6, J8.6, J9.6, J12.6, J13.6, U2.6, U2_R.6, U3.6, U3_R.6, U5.1, U5.2, pHAT.3, raspberry.3
OffSig: J3.11, J5.5, J6.11, J8.11, J9.11, J12.11, J13.11, U2.11, U2_R.11, U3.11, U3_R.11
P13: J3.13, J6.13, J8.13, J9.13, J12.13, J13.13, U2.13, U2_R.13, U3.13, U3_R.13
POff3: J2.4, J3.17, J6.17, J8.17, J9.17, J12.17, J13.17, U2.17, U2_R.17, U3.17, U3_R.17, pHAT.18, raspberry.18
POn3: J2.2, J3.16, J6.16, J8.16, J9.16, J12.16, J13.16, U2.16, U2_R.16, U3.16, U3_R.16, pHAT.16, raspberry.16
PWM: C3.1, J3.14, J4.3, J6.14, J8.14, J9.14, J12.14, J13.14, U2.14, U2_R.14, U3.14, U3_R.14, pHAT.31, raspberry.31
Poff: J2.3, J3.10, J6.10, J8.10, J9.10, J12.10, J13.10, U2.10, U2_R.10, U3.10, U3_R.10
Pon: J2.1, J3.9, J6.9, J8.9, J9.9, J12.9, J13.9, U2.9, U2_R.9, U3.9, U3_R.9
REnv: J3.5, J6.5, J8.5, J9.5, J12.5, J13.5, U2.5, U2_R.5, U3.5, U3_R.5
RPiN: J3.12, J5.2, J5.4, J5.6, J6.12, J8.12, J9.12, J12.12, J13.12, U2.12, U2_R.12, U3.12, U3_R.12, pHAT.29
Raw: J3.18, J6.18, J8.18, J9.18, J12.18, J13.18, U2.18, U2_R.18, U3.18, U3_R.18
RawSig: J3.4, J5.1, J6.4, J8.4, J9.4, J12.4, J13.4, U2.4, U2_R.4, U3.4, U3_R.4
VDD_3V3: C2.1, J3.19, J6.19, J8.19, J9.19, J12.19, J13.19, J14.1, MB102.6, MB102.8, U2.19, U2_R.19, U3.19, U3_R.19
VDD_3V3_PI: J14.2, pHAT.1, pHAT.17, raspberry.1, raspberry.17
VDD_5V: +5V.1, C1.1, J3.2, J4.2, J6.2, J7.1, J8.2, J9.2, J12.2, J13.2, MB102.2, MB102.4, U2.2, U2_R.2, U3.2, U3_R.2, U5.7, U5.8, pHAT.2, pHAT.4, raspberry.2, raspberry.4
j10_7: pHAT.7, raspberry.7
j10_8: pHAT.8, raspberry.8
j10_10: pHAT.10, raspberry.10
j10_11: pHAT.11, raspberry.11
j10_12: pHAT.12, raspberry.12
j10_13: pHAT.13, raspberry.13
j10_15: pHAT.15, raspberry.15
j10_19: pHAT.19, raspberry.19
j10_21: pHAT.21, raspberry.21
j10_22: pHAT.22, raspberry.22
j10_23: pHAT.23, raspberry.23
j10_24: pHAT.24, raspberry.24
j10_26: pHAT.26, raspberry.26
j10_27: pHAT.27, raspberry.27
j10_28: pHAT.28, raspberry.28
j10_32: pHAT.32, raspberry.32
j10_33: pHAT.33, raspberry.33
j10_35: pHAT.35, raspberry.35
j10_36: pHAT.36, raspberry.36
j10_37: pHAT.37, raspberry.37
j10_38: pHAT.38, raspberry.38

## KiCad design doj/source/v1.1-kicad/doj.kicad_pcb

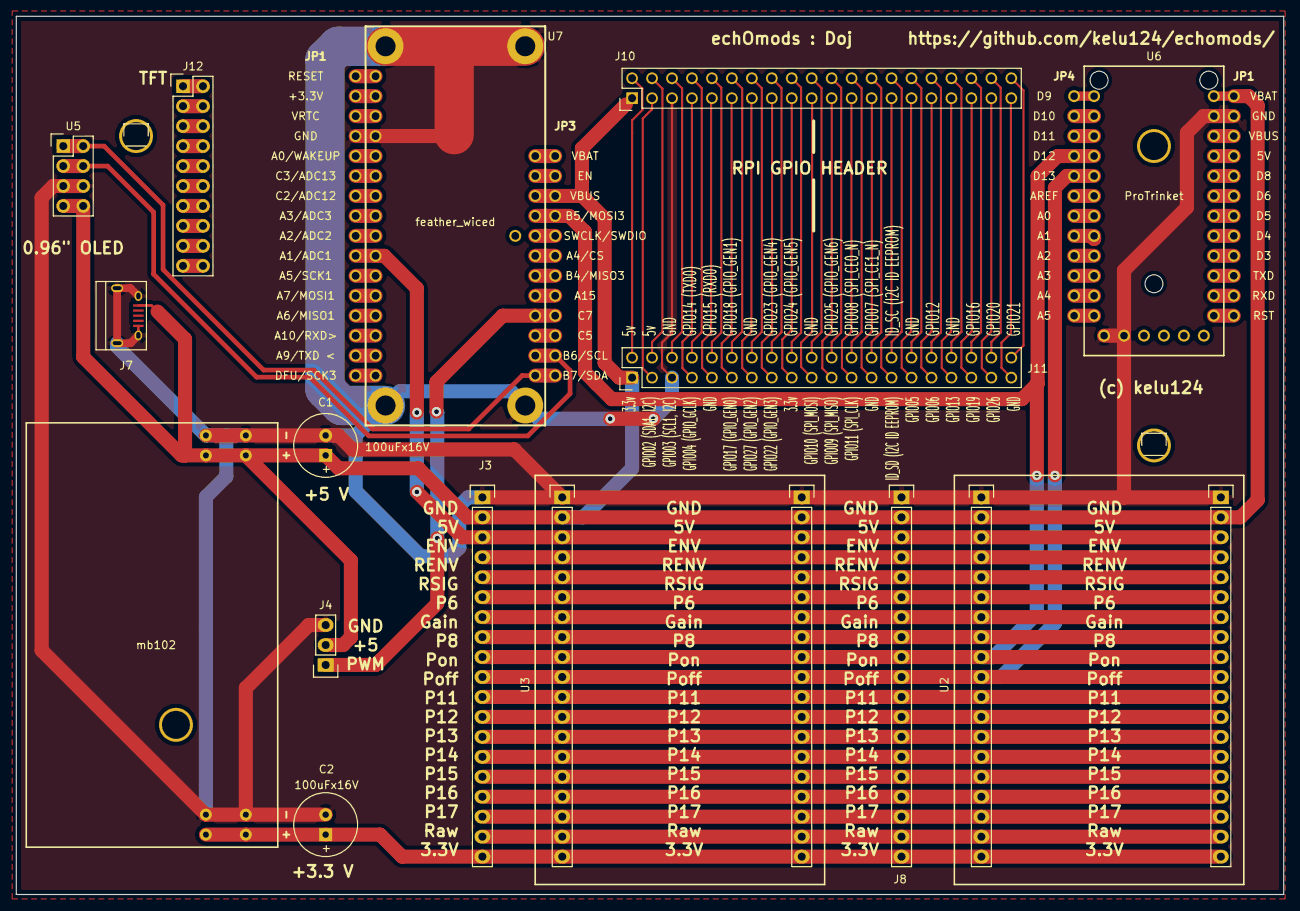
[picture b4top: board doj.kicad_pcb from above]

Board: 2 copper layers, 161.3 x 111.8 mm, 17 parts (0 on the bottom side), 70 nets.

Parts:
C1, C2: 100uFx16V; C1V8
J3, J8: Pin_Header_Straight_1x19
J4: Pin_Header_Straight_1x03
J7: USB_Micro-B
J10, J11: Pin_Header_Straight_2x20
J12: Pin_Header_Straight_2x10
MB102: mb102
U2, U2_R, U3, U3_R: Pin_Header_Straight_1x19
U5: Pin_Header_Straight_2x04
U6: ProTrinket; TrinketPro
U7: feather_wiced

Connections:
AGND: C1.2, C2.2, J3.1, J4.3, J7.5, J7.6, J8.1, J10.5, J11.5, MB102.1, MB102.3, MB102.5, MB102.7, U2.1, U2_R.1, U3.1, U3_R.1, U5.5, U5.6, U6.1, U6.2, U6.11, U7.0, U7.13
LCD_SCL: U5.3, U5.4, U7.11
LCD_SDA: U5.1, U5.2, U7.12
SERVO_PWM: J4.1, U7.9
U2_4: J3.4, J8.4, U2.4, U2_R.4, U3.4, U3_R.4
U2_5: J3.5, J8.5, U2.5, U2_R.5, U3.5, U3_R.5
U2_6: J3.6, J8.6, U2.6, U2_R.6, U3.6, U3_R.6
U2_7: J3.7, J8.7, U2.7, U2_R.7, U3.7, U3_R.7
U2_8: J3.8, J8.8, U2.8, U2_R.8, U3.8, U3_R.8
U2_11: J3.11, J8.11, U2.11, U2_R.11, U3.11, U3_R.11
U2_12: J3.12, J8.12, U2.12, U2_R.12, U3.12, U3_R.12
U2_13: J3.13, J8.13, U2.13, U2_R.13, U3.13, U3_R.13
U2_14: J3.14, J8.14, U2.14, U2_R.14, U3.14, U3_R.14
U2_15: J3.15, J8.15, U2.15, U2_R.15, U3.15, U3_R.15
U2_16: J3.16, J8.16, U2.16, U2_R.16, U3.16, U3_R.16
U2_17: J3.17, J8.17, U2.17, U2_R.17, U3.17, U3_R.17
U2_18: J3.18, J8.18, U2.18, U2_R.18, U3.18, U3_R.18
VDD_3V3: C2.1, J3.19, J8.19, MB102.6, MB102.8, U2.19, U2_R.19, U3.19, U3_R.19
VDD_5V: C1.1, J3.2, J4.2, J7.1, J8.2, J10.1, J11.1, MB102.2, MB102.4, U2.2, U2_R.2, U3.2, U3_R.2, U5.7, U5.8, U6.12, U7.3
fw_sigout: J3.3, J8.3, U2.3, U2_R.3, U3.3, U3_R.3, U7.7
j10_2: J10.2, J11.2
j10_3: J10.3, J11.3
j10_4: J10.4, J11.4
j10_6: J10.6, J11.6
j10_7: J10.7, J11.7
j10_8: J10.8, J11.8
j10_9: J10.9, J11.9
j10_10: J10.10, J11.10
j10_11: J10.11, J11.11
j10_12: J10.12, J11.12
j10_13: J10.13, J11.13
j10_14: J10.14, J11.14
j10_15: J10.15, J11.15
j10_16: J10.16, J11.16
j10_17: J10.17, J11.17
j10_18: J10.18, J11.18
j10_19: J10.19, J11.19
j10_20: J10.20, J11.20
j10_21: J10.21, J11.21
j10_22: J10.22, J11.22
j10_23: J10.23, J11.23
j10_24: J10.24, J11.24
j10_25: J10.25, J11.25
j10_26: J10.26, J11.26
j10_27: J10.27, J11.27
j10_28: J10.28, J11.28
j10_29: J10.29, J11.29
j10_30: J10.30, J11.30
j10_31: J10.31, J11.31
j10_32: J10.32, J11.32
j10_33: J10.33, J11.33
j10_34: J10.34, J11.34
j10_35: J10.35, J11.35
j10_36: J10.36, J11.36
j10_37: J10.37, J11.37
j10_38: J10.38, J11.38
j10_39: J10.39, J11.39
j10_40: J10.40, J11.40
j12_1: J12.1, J12.2
j12_3: J12.3, J12.4
j12_5: J12.5, J12.6
j12_7: J12.7, J12.8
j12_9: J12.9, J12.10
j12_11: J12.11, J12.12
j12_13: J12.13, J12.14
j12_15: J12.15, J12.16
j12_17: J12.17, J12.18
j12_19: J12.19, J12.20
track_pulse_a: J3.9, J8.9, U2.9, U2_R.9, U3.9, U3_R.9, U6.9, U7.4
track_pulse_b: J3.10, J8.10, U2.10, U2_R.10, U3.10, U3_R.10, U6.8
